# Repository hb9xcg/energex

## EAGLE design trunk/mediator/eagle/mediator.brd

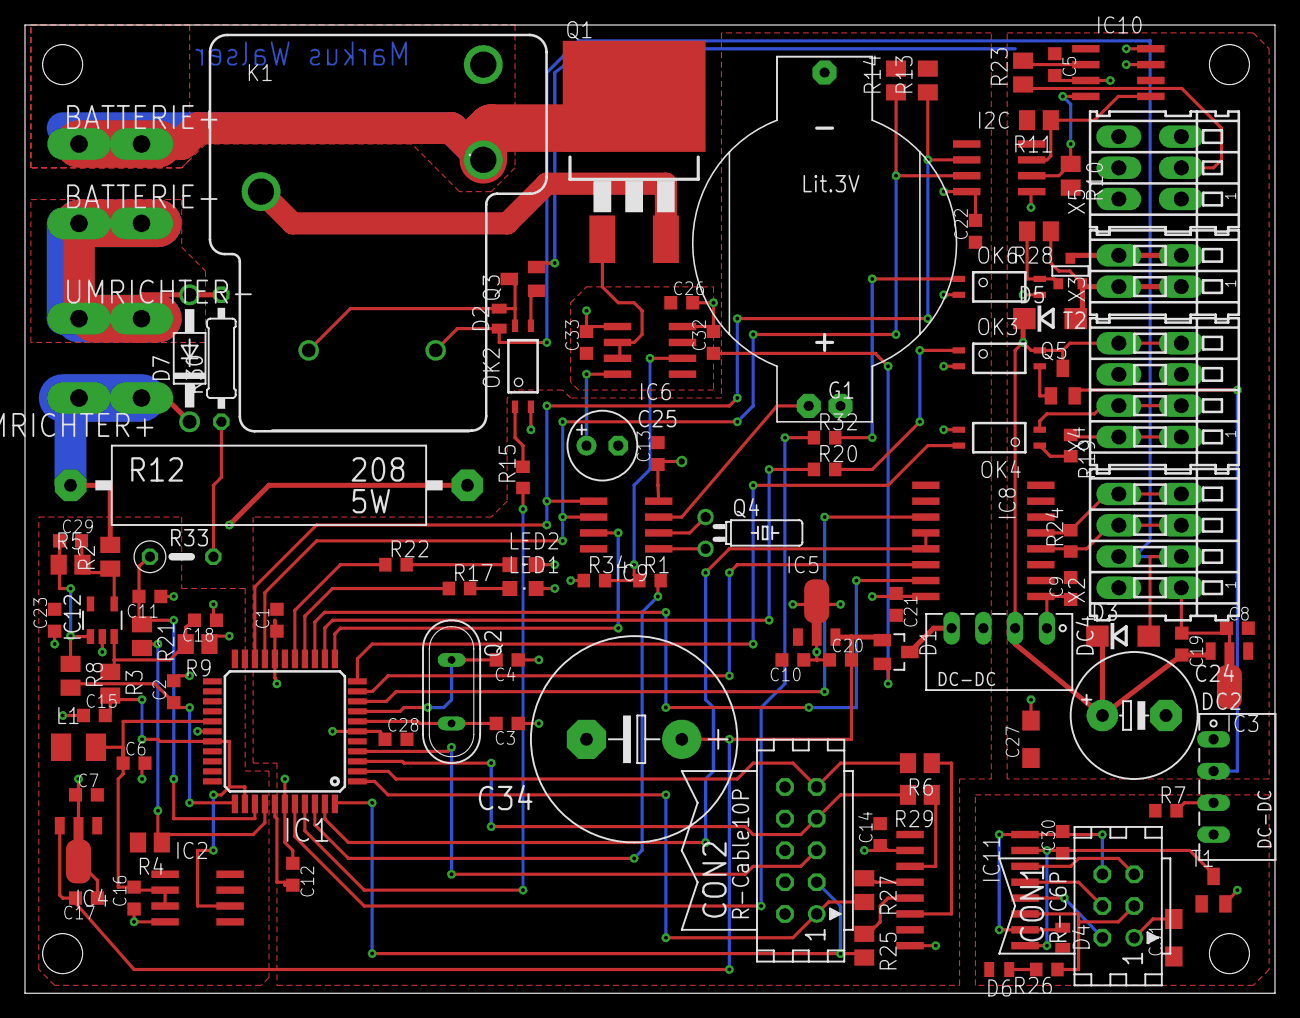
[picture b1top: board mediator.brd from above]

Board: 2 copper layers, 100.0 x 77.5 mm, 113 parts (1 on the bottom side), 83 nets.

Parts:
BATTERIE+: PIN2F061.100; F061.100
BATTERIE-: PIN2F061.100; F061.100
C1, C2, C5, C6, C7, C8, C9, C10, C11, C12, C13, C14, C15, C16, C17, C18, C19, C20, C21, C22, C23, C26, C28, C29, C30, C32: 100nF; C0603K
C3, C4: 18pF; C0603K
C24: 2200uF; E5-10,5
C25: 220uF; E2,5-6
C27, C31: 10uF; SMC_A
C33: 1uF; C0603K
C34: 6800uF; E7,5-16
CON1: CON06
CON2: CON10
D1: BAS40-06; SOT23
D2, D4, D6: 1N4148; MICROMELF-R
D3, D5: 1N4001; DO214AC
D7: 1N4004; DO41-10
DC2: NME1205SC; NME
DC4: NME1212SC; NME
G1: CR2032H
I2C: ADUM1250; SO8@1
IC1: ATMega644-A; TQFP44
IC2: REF192; SO08
IC3, IC4, IC5: 78L05; SOT89
IC6: MIC4420M; SO-08
IC8: ADM2483; SO16W
IC9: DS1307; SO08
IC10: DS2482-100; SO08
IC11: ADuM1401; SO16W
IC12: OPA735; SOT23-5
K1: JTN-PCB-DC12V; JT-PCB
L1: 10uH; L3225M
LED1: Red; CHIPLED_0805
LED2: Green; CHIPLED_0805
OK2, OK3, OK4, OK6: TLP281; MINI-FLAT-4
Q1: STB25NM50N; D2PACK
Q2: 16MHz; QS
Q3: BC817-16SMD; SOT23-BEC
Q4: 32768; TC26H
Q5: BC817-25LT1SMD; SOT23-BEC
R1, R22, R26: 1k; R0603
R2, R9: 1k5; M0805
R3, R5: 24k; M0805
R4: 2k4; M0805
R6, R25, R27, R29: 1k; M0805
R7: 4k7; R0603
R8, R10, R11, R13, R14, R28: 10k; M0805
R12: 0.005; KH208-8
R15, R17, R19, R20, R32: 1k2; R0603
R21: 3k92; M0805
R23: 100; M0805
R24: 120; R0603
R30: 332k; 0207/10
R33: 332k; 0207/5V
R34: 10k; R0603
T1: SOT23
T2: SOT-23
UMRICHTER+: PIN2F061.100; F061.100
UMRICHTER-: PIN2F061.100; F061.100
X2, X4: 233-104
X3: 233-102
X5: 233-203
~NUDEV~1: GND-GNDA

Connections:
+5V: C1.2, C10.2, C12.2, C13.2, C14.2, C21.2, C22.1, C28.2, CON2.2, I2C.1, IC1.5, IC1.17, IC1.38, IC5.1, IC8.1, IC9.8, IC11.1, IC11.7, R13.2, R14.2
+5V/2: C31.+, D4.A, D6.A, DC2.4, R7.1, T1.1
GND: C1.1, C3.1, C4.1, C10.1, C12.1, C13.1, C14.1, C20.1, C21.1, C22.2, C25.-, C26.2, C28.1, C32.2, C33.2, C34.-, CON2.4, CON2.6, CON2.8, CON2.10, DC4.3, G1.-, I2C.4, IC1.6, IC1.18, IC1.39, IC5.2, IC5.2.1, IC6.4, IC6.5, IC8.8, IC9.4, IC11.2, IC11.8, LED1.C, LED2.C, OK2.2, OK3.2, OK4.3, OK6.2, R34.1, ~NUDEV~1.GND
GND2: C31.-, CON1.1, DC2.3, R7.2, T1.2
GNDA: C2.2, C6.2, C7.1, C11.1, C15.1, C16.1, C17.1, C18.1, C23.1, IC1.28, IC2.4, IC4.2, IC4.2.1, IC12.2, K1.C, Q1.3, R9.1, R12.2, ~NUDEV~1.GNDA
GNDIO: C5.2, C8.1, C9.1, C19.1, C24.-, C27.-, DC2.1, DC4.1, I2C.5, IC3.2, IC3.2.1, IC8.9, IC10.3, IC10.7, IC10.8, OK6.3, Q3.E, X2.B1, X4.B3, X5.B3
unnamed: IC6.6, Q1.1
unnamed: BATTERIE+.A1, K1.NO, Q1.2
unnamed: IC9.1, Q4.2
unnamed: CON2.7, IC1.3, R29.2
unnamed: C18.2, IC12.3, R3.1, R9.2
unnamed: C29.2, IC12.4, R2.1, R5.2
unnamed: C29.1, IC12.1, R5.1, R8.1
unnamed: CON2.1, IC1.1, R27.2
unnamed: DC2.2, Q5.E
unnamed: CON2.3, IC1.44, R25.2
unnamed: C2.1, IC1.34, R8.2
unnamed: C3.2, IC1.7, Q2.2
unnamed: C4.2, IC1.8, Q2.1
unnamed: I2C.6, IC10.4, R10.1
unnamed: I2C.7, IC10.5, R11.1
unnamed: D7.C, R2.2, R12.1, UMRICHTER+.A1
unnamed: IC10.2, R23.2
unnamed: BATTERIE-.A1, D7.A, R30.2, UMRICHTER-.A1
unnamed: IC1.37, R4.1, R21.2
unnamed: OK2.3, Q3.B
unnamed: OK2.1, R15.2
unnamed: C6.1, C16.2, IC1.27, IC2.2, IC2.3, L1.2
unnamed: I2C.2, IC1.20, IC9.5, R13.1
unnamed: I2C.3, IC1.19, IC9.6, R14.1
unnamed: IC1.41, R15.1
unnamed: D2.C, D3.A, K1.1, X2.B2
unnamed: IC1.15, R17.1
unnamed: D2.A, K1.2, OK2.4, Q3.C
unnamed: IC1.9, IC8.3
unnamed: CON2.9, IC1.2, R6.2
unnamed: IC1.42, R1.2
unnamed: IC11.6, R6.1
unnamed: D5.A, R28.1, T2.2, X3.B1
unnamed: IC1.10, IC8.6
unnamed: CON1.2, IC11.12
unnamed: IC8.13, R24.2, X2.B4
unnamed: IC1.16, R22.1
unnamed: IC8.12, R24.1, X2.B3
unnamed: IC1.43, IC8.4, IC8.5
unnamed: IC1.14, IC8.7
unnamed: R23.1, X5.B2
unnamed: R30.1, R33.2
unnamed: T2.1, X3.B2
unnamed: C30.1, IC11.9, IC11.15, T1.3
unnamed: OK3.3, Q5.B
unnamed: OK3.1, R20.2
unnamed: IC1.13, R20.1
unnamed: IC1.11, OK4.4
unnamed: OK4.2, X4.B2
unnamed: OK4.1, R19.2
unnamed: G1.+, IC9.3
unnamed: CON1.3, IC11.11, R26.1
unnamed: CON1.4, IC11.13
unnamed: CON2.5, IC1.4
unnamed: CON1.5, IC11.14
unnamed: LED1.A, R17.2
unnamed: R19.1, X4.B1
unnamed: C15.2, IC1.29, IC1.35, IC2.6, R3.2
unnamed: IC1.12, IC9.7
unnamed: C30.2, CON1.6, D4.C, IC11.10, IC11.16
unnamed: C17.2, C20.2, C34.+, D1.1, IC4.3, IC5.3
unnamed: IC9.2, Q4.1
unnamed: LED2.A, R22.2
unnamed: IC6.2, R1.1, R34.2
unnamed: D1.3, DC4.4
unnamed: C11.2, IC1.36, R21.1, R33.1
unnamed: D6.C, R26.2
unnamed: IC11.5, R25.1
unnamed: IC11.4, R27.1
unnamed: IC11.3, R29.1
unnamed: OK6.4, R28.2, T2.3
unnamed: OK6.1, R32.2
unnamed: IC1.40, R32.1
VCC: C25.+, C26.1, C32.1, C33.1, D1.2, IC6.1, IC6.8
VCCINT: C19.2, C24.+, D3.C, D5.C, DC4.2, IC3.3, OK3.4, Q5.C, X4.B4
VCCIO: C5.1, C8.2, C9.2, C27.+, I2C.8, IC3.1, IC8.16, IC10.1, R10.2, R11.2, X5.B1
VDD: C7.2, C23.2, IC4.1, IC12.5, L1.1, R4.2

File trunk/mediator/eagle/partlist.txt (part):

Partlist

Exported from mediator.sch at 17.08.10 19:35

EAGLE Version 5.8.0 Copyright (c) 1988-2010 CadSoft

Part       Value          Device            Package      Library          Sheet

BATTERIE+  PIN2F061.100   PIN2F061.100      F061.100     con-faston       1	Bestellung Farnell
BATTERIE-  PIN2F061.100   PIN2F061.100      F061.100     con-faston       1	Bestellung Farnell
C1         100nF          C-EUC0603K        C0603K       rcl              1	vorhanden
C2         100nF          C-EUC0603K        C0603K       rcl              1	vorhanden
C3         18pF           C-EUC0603K        C0603K       rcl              1	vorhanden
C4         18pF           C-EUC0603K        C0603K       rcl              1	vorhanden
C5         100nF          C-EUC0603K        C0603K       rcl              1	vorhanden
C6         100nF          C-EUC0603K        C0603K       rcl              1	vorhanden
C7         100nF          C-EUC0603K        C0603K       rcl              1	vorhanden
C8         100nF          C-EUC0603K        C0603K       rcl              1	vorhanden
C9         100nF          C-EUC0603K        C0603K       rcl              1	vorhanden
C10        100nF          C-EUC0603K        C0603K       rcl              1	vorhanden
C11        100nF          C-EUC0603K        C0603K       rcl              1	vorhanden
C12        100nF          C-EUC0603K        C0603K       rcl              1	vorhanden
C13        100nF          C-EUC0603K        C0603K       rcl              1	vorhanden
C14        100nF          C-EUC0603K        C0603K       rcl              1	vorhanden
C15        100nF          C-EUC0603K        C0603K       rcl              1	vorhanden
C16        100nF          C-EUC0603K        C0603K       rcl              1	vorhanden
C17        100nF          C-EUC0603K        C0603K       rcl              1	vorhanden
C18        100nF          C-EUC0603K        C0603K       rcl              1	vorhanden
C19        100nF          C-EUC0603K        C0603K       rcl              1	vorhanden
C20        100nF          C-EUC0603K        C0603K       rcl              1	vorhanden
C21        100nF          C-EUC0603K        C0603K       rcl              1	vorhanden
C22        100nF          C-EUC0603K        C0603K       rcl              1	vorhanden
C23        100nF          C-EUC0603K        C0603K       rcl              1	vorhanden
C24        2200uF         CPOL-EUE5-10.5    E5-10,5      rcl              1	vorhanden
C25        220uF          CPOL-EUE2.5-6     E2,5-6       rcl              1	Bestellung Farnel
C26        100nF          C-EUC0603K        C0603K       rcl              1	vorhanden
C27        10uF           CPOL-EUSMCA       SMC_A        rcl              1	vorhanden (2 Stück)
C28        100nF          C-EUC0603K        C0603K       rcl              1	vorhanden
C29        100nF          C-EUC0603K        C0603K       rcl              1	vorhanden
C30        100nF          C-EUC0603K        C0603K       rcl              1	vorhanden
C31        10uF           CPOL-EUSMCA       SMC_A        rcl              1	vorhanden (2 Stück)
C32        100nF          C-EUC0603K        C0603K       rcl              1	vorhanden
C33        1uF            C-EUC0603K        C0603K       rcl              1	vorhanden (8 Stück)
C34        6800uF         CPOL-EUE7.5-16    E7,5-16      rcl              1	Bestellung Farnell
CON1                      CON06             CON06        con-harting      1	vorhanden
CON2                      CON10             CON10        con-harting      1
D1         BAS40-06       BAS40-06          SOT23        diode            1	vorhanden
D2         1N4148         DIODE-MICROMELF-R MICROMELF-R  diode            1	vorhanden (6 Stück)
D3         1N4148         DIODE-MICROMELF-R MICROMELF-R  diode            1	vorhanden (6 Stück)
D4         1N4148         DIODE-MICROMELF-R MICROMELF-R  diode            1	vorhanden (6 Stück)
D6         1N4148         DIODE-MICROMELF-R MICROMELF-R  diode            1	vorhanden (6 Stück)
D7         1N4004         1N4004            DO41-10      diode            1
DC2        NME1205SC      NME               NME          dc-dc-converter  1	vorhanden
DC4        NME1212SC      NME               NME          dc-dc-converter  1	vorhanden
G1         CR2032H        CR2032H           CR2032H      mediator         1	vorhanden
I2C        ADUM1250       ADUM1250          SO8          analog-devices   1
IC1        ATMega644-A    MEGA32-A          TQFP44       atmel            1	Bestellung Farnell ATMega-644p (2 ATMega644 vorhanden)
IC2        REF192         REF192            SO08         icontroller      1	vorhanden
IC3        78L05          78L05             SOT89        icontroller      1	unterwegs
IC4        78L05          78L05             SOT89        icontroller      1	unterwegs
IC5        78L05          78L05             SOT89        icontroller      1	unterwegs
IC6        MIC4420M       MIC4420M          SO-08        transistor-power 1	Bestellung Farnell
IC8        ADM2483        ADM2483           SO16W        icontroller      1	vorhanden
IC9        DS1307         DS1307            SO08         icontroller      1	vorhanden
IC10       DS2482-100     DS2482-100        SO08         icontroller      1	vorhanden
IC11       ADuM1401       ADUM1401          SO16W        spisolator       1	vorhanden
IC12       OPA735         OPA743            SOT23-5      linear           1	unterwegs
K1         JTN-PCB-DC12V  JTN-PCB-DC12V     JT-PCB       relay            1	vorhanden
L1         10uH           L-EUL3225M        L3225M       rcl              1	vorhanden
LED1       Red            LEDCHIPLED_0805   CHIPLED_0805 led              1	vorhanden
LED2       Green          LEDCHIPLED_0805   CHIPLED_0805 led              1	vorhanden
OK2        TLP281         TLP283            MINI-FLAT-4  optocoupler      1	unterwegs (3 Stück)
OK3        TLP281         TLP283            MINI-FLAT-4  optocoupler      1	unterwegs (3 Stück)
OK4        TLP281         TLP283            MINI-FLAT-4  optocoupler      1	unterwegs (3 Stück)
OK6        TLP281         TLP283            MINI-FLAT-4  optocoupler      1
Q1         STGB12NB60KD   IRG4BC15UD-S      D2PACK       transistor-power 1	vorhanden
Q2         16MHz          XTAL/S            QS           special          1	vorhanden
Q3         BC817-16SMD    BC817-16SMD       SOT23-BEC    transistor-npn   1	vorhanden (4 Stück)
Q4         32768          CRYSTALTC26H      TC26H        crystal          1	vorhanden
Q5         BC817-25LT1SMD BC817-25LT1SMD    SOT23-BEC    transistor-npn   1	vorhanden (4 Stück)
Q6         BC817-25LT1SMD BC817-25LT1SMD    SOT23-BEC    transistor-npn   1	vorhanden (4 Stück)
R2         1k5            R-EU_M0805        M0805        rcl              1	Bestellung Farnell (0.1%)
R3         24k            R-EU_M0805        M0805        rcl              1	Bestellung Farnell (0.1%)
R4         2k4            R-EU_M0805        M0805        rcl              1	vorhanden
R5         24k            R-EU_M0805        M0805        rcl              1	Bestellung Farnell (0.1%)
R6         1k             R-EU_M0805        M0805        rcl              1	vorhanden
R7         4k7            R-EU_R0603        R0603        rcl              1	vorhanden
R8         10k            R-EU_M0805        M0805        rcl              1	vorhanden
R9         1k5            R-EU_M0805        M0805        rcl              1	Bestellung Farnell (0.1%)
R10        10k            R-EU_M0805        M0805        rcl              1	vorhanden
R11        10k            R-EU_M0805        M0805        rcl              1	vorhanden
R12        0.005          RKH208-8          KH208-8      resistor-power   1	vorhanden
R13        10k            R-EU_M0805        M0805        rcl              1	vorhanden
R14        10k            R-EU_M0805        M0805        rcl              1	vorhanden
R15        1k2            R-EU_R0603        R0603        rcl              1	vorhanden
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
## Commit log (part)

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2008-08-08 Completed frame (un-)stuffing.
2008-08-08 Use just one battery internally and pretend as having three of them.
2008-08-08 Added Twike protocol.
2008-08-10 Added voltage and temperature sampling.
2008-08-12 Added stop interrupt to power-off the Twike.
2008-08-19 First solution for simplex RS485 instead of RS422 full-duplex: Simply flush all incomming bytes during transmission.
2008-08-19 Added DriveState and BInfo.
2008-08-19 Added DriveState and BInfo. Made battery accesses thread safe.
2008-08-21 Added datasheets.
2008-09-14 * Replaced SO-8 voltage regulators by SOT-89. * Added RTC to I2C bus. * Added hardware support for RS485 instead of RS422.
2008-09-14 * Added red and green LEDs. * Cleaned up ground routing around external I2C connecter.
2008-09-16 * Added emergency input on the slave bus. * Added emergency output used for Notaus relais.
2008-10-04 Successor of the icontroller to control the daisy chain.
2008-10-04 Setup initial mediator.
2008-10-05 Initial daisy version.
2008-10-15 * Isolierter One-Wire Bus hinzugefügt. * Kleinerer DC/DC Wandler für One-Wire Bus. * Stecker neu angeordnet. * Spannungsmessung vereinfacht. * Weitere Groundplanes eingeführt. * uP hängt neu auf dem 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
2008-10-17 * Zusätzliche Stützkondensatoren eingebaut. * RS485 Abschlusswiderstand hinzugefügt.
2008-10-17 * Weitere verwendete Datenblätter importiert.
2008-10-17 * Partlist hinzugefügt. * RTC Quarz Bauform gewechselt.
2008-10-17 * Weitere Stützkondensatoren. * Kleinere Aufräumarbeiten.
2008-10-28 Minor cleanups.
2008-10-28 Release preparation.
2008-10-28 Revision 0.3 sent to Q-PCB.
2008-11-16 * Changed IO configuration to the new mediator board rev. 0.3 * Introduced real RS485 with HW support. Interface should be Twike compatible now. * Added external reference voltage. * Adapted ADC spee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
2008-11-28 * Namespace cleanups. * Switch relais according to the CMD parameter. * Increased relais delay time to 500ms. * Send BInfo to the Twike boardcomputer. * Completed temperature measurement. * Corrected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
2008-12-02 * Added recorded RS485 log files of driving and charge-startup phase. * Added ATMega644P datasheet.
2008-12-02 * Fixed doubled checksum if checksum has frame value 0x10. * Better log output.
2008-12-02 * Corrected frame unstaffing.
2009-02-20 Added charge sequence analysis.
2009-02-28 Added schema image
2009-03-22 Added LTC6802-1 device.
2009-03-24 First version able to charge and drive with NiCd Akku:
    * Added CRC check to one wire temperature sensor.
    * Added extended temperature format to one wire temperature sensor.
    * Added differential current measurement.
    * Added automatic offset compensation to current measurement.
    * Added persistent storage of capacity.
    * Added lots of BINFO checks.
2009-04-14 Added soft reboot command.
2009-04-17 Feature: * Added boot loader support for mediator.
    Bugfix:
    * Corrected current measurement.
    * Corrected saving of the settings during exit of application.
    Cleanup:
    * Re-added rxtx binaries to simplify distribution.
2009-04-25 Better boot loader connection sequence.
2009-08-17 Corrected LTC6802-1 package.
2009-10-10 Added partlist.
2009-10-10 Simplified filenames.
2009-10-10 Changed to 12-cell surveillance.
2009-10-10 Tagged revison 0.3 of supervisor which went to production.
2009-11-29 Added NTC temperature converter.
2009-12-04 Added make file.
2009-12-04 Added spi module.
2009-12-14 Added o-scope functionality to log charge current.
2010-01-03 Give more verbose branch name.
2010-02-18 Prepare trunk for C++ QTwikeAnalyzer version by moving Qt Jambi version to separate branch.
2010-02-18 Initial version of C++ QTwikeAnalizer.
2010-02-18 Removed automatically generated files and some stale debug code.
2010-02-20 Added license
2010-02-20 * Added automatical power off with data primarily storage. * Implemented more accurate current measurement.
2010-02-20 fixed kontrollerlab build
2010-02-22 Fixed online recording.
2010-02-24 Reverted psychoquaker's accidentally committed r140.
2010-02-25 Added lock properties.
2010-02-27 Initial release used on mediator 0.4.
2010-03-04 Almost complete rework of mediator: * Added isolated SPI used for supervisor daisy chain. * Simplyfied current measurement. * Removed analogue temperature sensor. * (Hopefully) fixed IGBT damage. * A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
2010-03-04 * Removed old schematic graphics. * Increased value of secondary blackout capacitor.
2010-03-12 * Added OneWire power lane. * Replaced battery with battery clip. * Minor layout improvements.
2010-03-14 Create release folder.
2010-03-14 Released version 0.4 of QTwikeAnalyzer.
2010-03-14 Corrected rpm build.
2010-03-14 Picked rev 165 from trunk: Fixed rpm build.
2010-03-14 Overhauled SPI galvanic isolation.
2010-03-21 First "routable" version of TwixBC (Twike Battery Controller) online.
    - removed AGND (only one groundplane in this layout which is connected to (Twike-) mains (negative))
    - rearranged parts
    - removed connection errors at OPAMP
2010-05-05 LTC_Balancer:
    - board available
    - changes in battery connector and interface isolation
2010-06-05 Fixed decoding of "transmit data" packet.
2010-07-09 Enlarged LTC6802 pads for easier manual soldering.
2010-07-09 Updated partlist to Supervisor revision 0.3.1 / 0.4.
2010-07-09 Tagged release 0.4 with enlarged pads for easier manual soldering.
2010-07-09 Move revision 0.4 of supervisor to correct place.
2010-07-26 Initial version of power line controller.
2010-07-26 Initial version of powerline controller.
2010-07-26 Initial datasheets.
2010-07-26 Initial documentation folder.
2010-07-26 Corrected datasheet folder structure.
2010-07-26 Initial firmware folder.
2010-08-21 * Reworked SPI gateway * Added dedicated controller for IGBT gate. * Allow more power on emergency switch (up to 5A). * Reduced power consumption. * Better 12V blackout handling.
2010-08-27 * Corrected emergency stop circuit.
2010-09-14 * Exchanged port SS with PB0.
2010-09-17 * Hardware version released for production.
2010-09-17 Created power line controller tags folder.
2010-09-17 Hardware version released for production.
2010-09-17 * Some minor text correction.
2010-10-19 Added block diagram.
2010-10-25 * Fixed firmware update when image wasn't correctly aligned to ATMega644p's page size of 256byte. * Added new feature to distinguish between Mediator and PLC firmware update.
2010-12-23 * Adapted to Mediator hardware revision 1.0. * Added cell balancing. * Added RTC support. * Added more persistent data. * Added NTC temperature sensor linearization * Added initial version of a lithi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
2010-12-23 * Added mediator revision 0.4 and revision 1.0 fuse bits.
2010-12-23 Contains several bug fixes and cleanups: * Removed sensor stack usage print out. * Fixed some thread safety issues. * Corrected temperature report to the Twike board computer. * Corrected battery ind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
2010-12-23 * Ignore automatically generated files.
2011-01-08 * Changed Supervisor design from LTC6802-1 to LTC6802-2 for better EMI robustness.
2011-01-09 * Added LTC6802-2 datasheet * Added additional mosfet to ensure proper GND on SPI isolation. * Corrected cell 12 connection. * Minor cleanups.
2011-01-18 * Added additional pullup resistor R53.
2011-02-09 * Adjusted wire position at two ltc6802-2 pins. * Reduced value of R52 from 1M to 100k to be on the safe side concerning leakage current of optocoupler. * Reduced jumper text to increase isolation.
2011-02-10 Added more datasheets
2011-02-12 Tagged version 0.5.
2011-02-12 * Increased GND plane isolation to 13mil (0.33mm) * Added different GND plane with 5 mil isolation on digital IO side. * Moved documentation from top copper layer to top docu layer. * Further cleanup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
2011-02-13 * Minor routing cleanup around T13 und R53.
2011-02-13 * Version 0.6 preparing production.
2011-02-13 * Tagged version 0.6.
2011-02-20 * Moved SMT devices on digital IO side to top layer. * Increased version to revision 0.8.
2011-02-20 * Fixed missing connection between R51 and C21. * Minor text placment changes for A0...A3.
2011-02-21 * Increased GND plane isolation from 15 to 16mil resp. from 5 to 6mil. * Added some more vias to fill GND plane. * Added project name on silk screen. * Updated part list (2 Watt resistors and version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
2011-02-23 * Move pull up resistor from GND to each data line. * Use 470 instead of 475 Ohm resistors for the LEDs.
2011-03-01 * Replaced 0603 package by 0402 package on the following resistors: R49, R50 (3k9) R52, R53, R54, R55, R60, R61 (100k) R57, R58, R59 (1M)
2011-03-08 * Increased version number in schematics.
2011-03-08 * Tagged version going to be manufactured.
2011-03-08 Added mediator base folder.
2011-03-08 * Cleanup folder structure.
2011-03-08 Added QTwikeAnalyzer base folder.
2011-03-08 * Further cleanup folder structure.
2011-04-21 * Added BINFO command. * Stop balancer thread during flash command. * Added some command help.
2011-04-21 * Adapted code to addressed behavior of LTC6802-2. * Removed unused delay between temperature and voltage measurement.
2011-04-21 * Enabled under/over voltage check and cable break check.
2011-04-22 Removed stale project: The mediator is the successor of the icontroller.
2011-04-22 Prepared code for first test drive: * Report general error to twike board computer. * Enabled balancer during charge phase. * Removed daisy chain test code.
2011-05-12 * Fine tuning charge process allowing DX charge (90%) and normal charge (75%). * Reenabled cable check as SPI bus is working reliable now. * Enable fans during cell balancing. * For now disabled IGBT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
2011-05-12 * Removed dependency to ko. * Abort charge if BINFO contains bit CHARGE_NOK. * Keep power during sym charge. * Show relais status with flashing LED. * Do not restart charge if battery is full.
2011-05-12 * Fixed invalid voltage measurement after warm start.
2011-06-13 Version used on Whit Monday: * Extended charge capacity to 4.15V per cell. * Added patch for defect ATMega port (disabled by default).
2011-09-26 * Take Supervisor bus supply from VCCINT to avoid communication interrupts when emergency stop is pressed.
2011-09-26 Tagged Mediator revision 1.1.
2011-10-02 * Implemented new port enumerator provided by qextserialport. * Removed no longer needed threads. * Speed up firmware download.
2012-02-27 * Adapted to Qwt version 6 api.
2012-02-27 * Increased version info.
2012-05-27 * Corrected total Ah counter.
2012-05-27 * Switch on Mosfet a bit earlier.
2012-05-27 * Changed firmware to new 3x3 motor firmware version.
2012-05-28 Created wiki page through web user interface.
2012-11-14 Edited wiki page Home through web user interface.
2013-01-24 Added picture.
2013-01-24 Edited wiki page Supervisor through web user interface.
2013-02-01 Added HW overview image.
2013-02-01 Added hardware overview.
2013-02-23 Added some Mediator pictures.
2013-02-23 Fixed typo.
2013-02-23 Added some pictures about QTwikeAnalyzer.
2013-03-30 Added mediator bootloader which works together with QTwikeAnalyzer.
2013-04-26 Adapted PROGMEM and ISR to new gcc/libc.
2013-04-27 Initialize fifo before interrupt are running.
2013-05-06 Removed lock property because google doesn't support it.
2013-05-06 Corrected power transistor type.
2014-03-14 Report low cell voltage with Twike Warning LED Report unbalanced battery stack with flashing Twike Warning LED.
2014-03-14 Fixed debug interface for temperature sensors.
2014-03-14 Lowered cell low voltage level. It's now used as end of discharge level (3.0V).
2014-03-14 Bugfix: The total Ah counter was not incremented on short drives below 1Ah. This commit makes the necessary variables persistant in the EEPROM.
2014-03-14 Removed stale code.
2015-04-14 Report total Ah counter with increments of 1Ah instead of 3Ah.
